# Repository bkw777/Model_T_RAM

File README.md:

# Model_T_RAM
8K RAM module for "Model T Computers"  
* TRS-80 Model 100  
* Kyotronic KC-85  
* NEC PC-8201  
* Olivetti M10  

Gerbers available in [releases](../../releases/latest).

[PCB from OSHPark](https://oshpark.com/shared_projects/dh91gDhY)  
[PCB from PCBWAY](https://www.pcbway.com/project/shareproject/Model_T_RAM.html)

[BOM from DigiKey](https://www.digikey.com/short/vbnv3rnf)

[How to do the legs](https://gist.github.com/bkw777/52d85d89eeff8445cc667685d05ea94d)  

The DIP row spacing is actually 725 mils not 700. It makes it annoying to solder because the rows don't line up exactly with the rows in a breadboard, but it's not an error.  
Using a set of single row socket headers in the breadboard, or even two stacked, allows the socket headers to spread a little and make it easier to hold the pins and pcb for soldering, and the finished soldered pins aren't pinched inwards too badly.

----
Thanks to Steve Adolph for advice about RAM_RST

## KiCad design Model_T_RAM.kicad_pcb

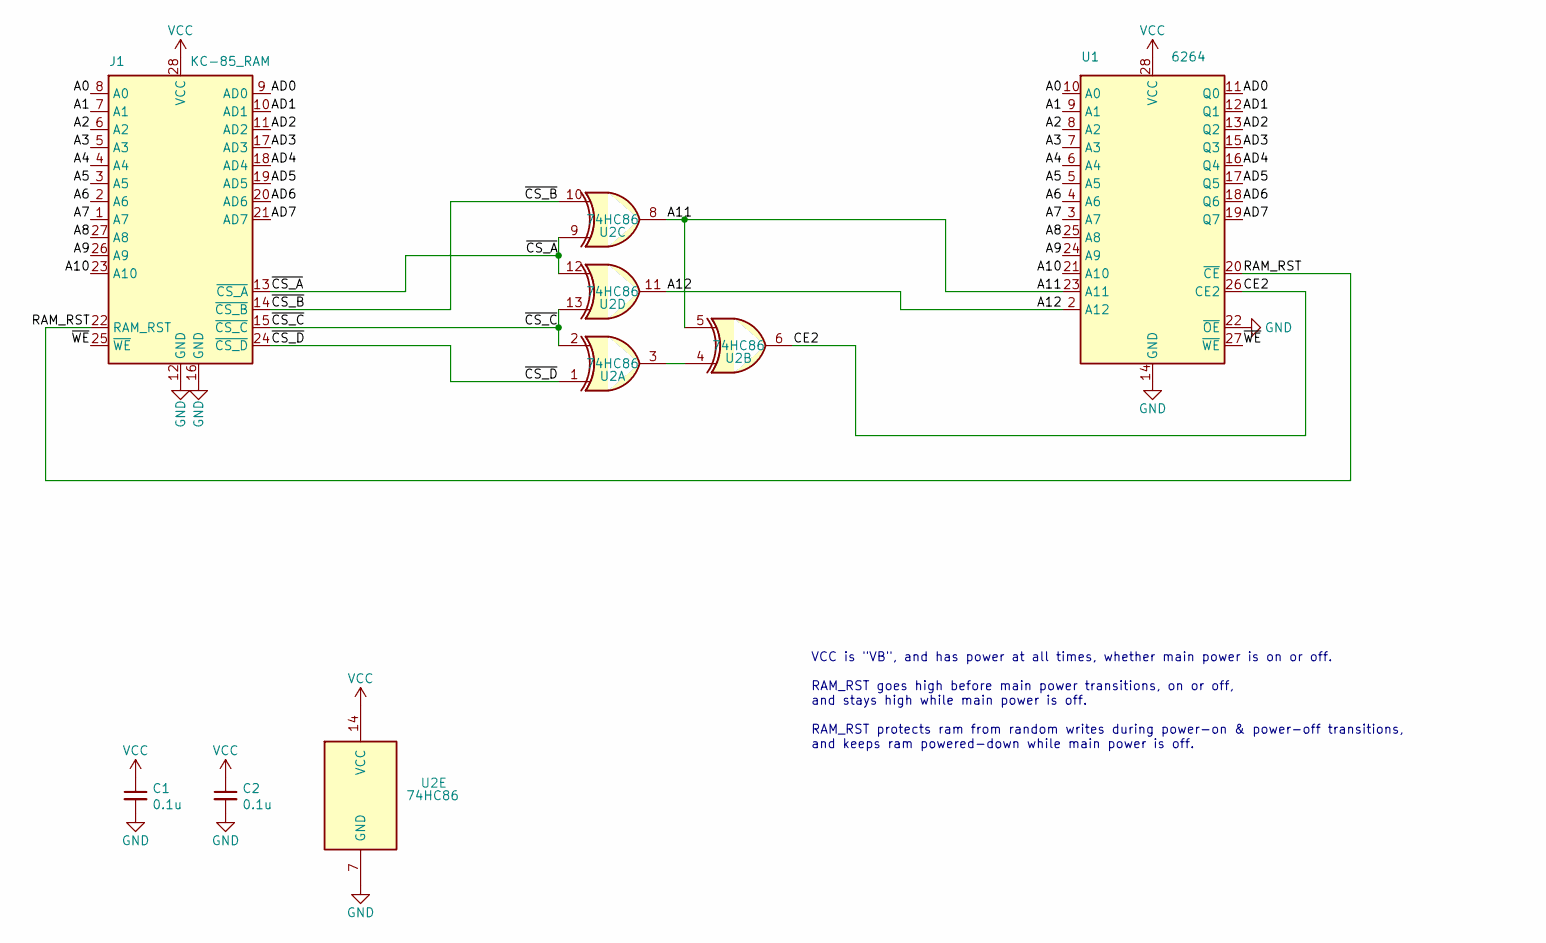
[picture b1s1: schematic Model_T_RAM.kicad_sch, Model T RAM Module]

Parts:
C1, C2: 0.1u; C_0805
J1: KC-85_RAM; DIP28_725mils_pcb_pins
U1: 6264; SSOP-28
U2: 74HC86; SOIC-14_4x9

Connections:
/A0: J1.8 (A0), U1.10 (A0)
/A1: J1.7 (A1), U1.9 (A1)
/A2: J1.6 (A2), U1.8 (A2)
/A3: J1.5 (A3), U1.7 (A3)
/A4: J1.4 (A4), U1.6 (A4)
/A5: J1.3 (A5), U1.5 (A5)
/A6: J1.2 (A6), U1.4 (A6)
/A7: J1.1 (A7), U1.3 (A7)
/A8: J1.27 (A8), U1.25 (A8)
/A9: J1.26 (A9), U1.24 (A9)
/A10: J1.23 (A10), U1.21 (A10)
/A11: U1.23 (A11), U2.5, U2.8
/A12: U1.2 (A12), U2.11
/AD0: J1.9 (AD0), U1.11 (Q0)
/AD1: J1.10 (AD1), U1.12 (Q1)
/AD2: J1.11 (AD2), U1.13 (Q2)
/AD3: J1.17 (AD3), U1.15 (Q3)
/AD4: J1.18 (AD4), U1.16 (Q4)
/AD5: J1.19 (AD5), U1.17 (Q5)
/AD6: J1.20 (AD6), U1.18 (Q6)
/AD7: J1.21 (AD7), U1.19 (Q7)
/CE2: U1.26 (CE2), U2.6
/RAM_RST: J1.22 (RAM_RST), U1.20 (~CE)
/~CS_A: J1.13 (~CS_A), U2.9, U2.12
/~CS_B: J1.14 (~CS_B), U2.10
/~CS_C: J1.15 (~CS_C), U2.2, U2.13
/~CS_D: J1.24 (~CS_D), U2.1
/~WE: J1.25 (~WE), U1.27 (~WE)
GND: C1.2, C2.2, J1.12 (GND), J1.16 (GND), U1.14 (GND), U1.22 (~OE), U2.7 (GND)
unnamed: U2.3, U2.4
VCC: C1.1, C2.1, J1.28 (VCC), U1.28 (VCC), U2.14 (VCC)

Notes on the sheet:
VCC is "VB", and has power at all times, whether main power is on or off. RAM_RST goes high before main power transitions, on or off, and stays high while main power is off. RAM_RST protects ram from random writes during power-on & power-off transitions, and keeps ram powered-down while main power 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

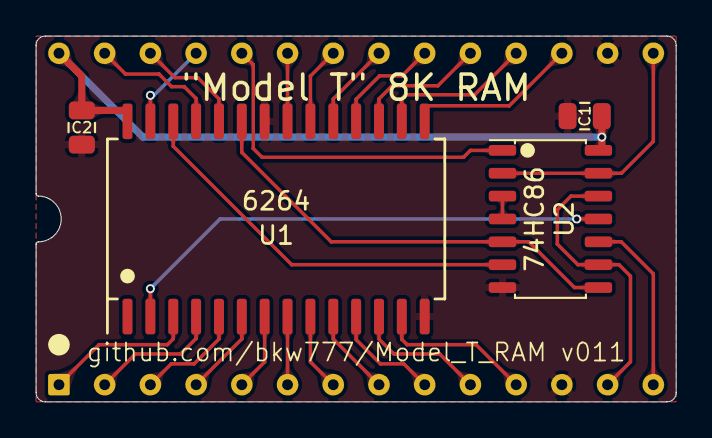
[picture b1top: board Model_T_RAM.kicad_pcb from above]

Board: 2 copper layers, 35.6 x 20.3 mm, 5 parts (0 on the bottom side), 31 nets.

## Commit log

2021-04-13 initial, gitignore & license
2021-04-13 initial
2021-04-13 readme
2021-04-20 v002 fewer vias
2021-04-20 tiny tidying
2021-04-20 switch to 74HC08
2021-04-20 tiny tidy
2021-04-21 remove 74HC86 b version
2021-04-21 tidy
2021-08-05 prettify schematic, note power problem, mothball
2021-08-05 note RAM_RST
2021-08-05 update schematic export
2021-08-05 switch to 74HC86 to sleep on standby
2021-08-05 rotate 7486
2021-08-06 RAM_RST on /CE instead of /OE
2021-08-09 update bom
2021-08-19 decoupling and ground pour
2021-08-19 bom & readme
2021-08-20 gold plated brass wire
2021-09-14 better routing and shielding
2022-09-13 kicad6. 725mil row spacing. pin models.
2022-09-21 add type b variant
2023-08-07 kicad 7
